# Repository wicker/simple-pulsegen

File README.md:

## Super Simple Function Generator

#### Waveform Generator IC

First off, I want to use a waveform generator IC. It seems like oscillators, audio waveform generators, and pulse generators are all limited kinds of waveform generator ICs. They all seem to cost less than the $10 chip I ended up with.

As far as full waveform generators go, the ICL8038 had an output frequency of up to 300kHz, and the derived MAX038 had an output frequency of up to 20MHz. Both chips are out of stock and no longer manufactured, so they're not an option for this project. 

I'm going to explore PLLs later on but for now I just want a chip that Just Works because the important thing is to generate my own signals. I could use the AD9833 or AD5930, both of which use direct digital synthesis (DDS) that converts a digital signal into an analog waveform.  

It's a tossup between AD9833 and AD5930. They both have 10 bit resolution and run on the same input range between 2.3V to 5.5V. 

AD9833 depends on 25MHz clock and is immediately available in quantity 1 for $9.27 at Digikey. 

AD5930 depends on a 50MHz clock and is not immediately available, and in any case it costs $13.40. And lo, another engineering decision decides itself. 

#### Using the AD9833 

It will produce sine, triangular, and square waves. No external components needed, except that it needs a microcontroller. The analog and digital grounds will need to be separated. It can create sine waves up to 12.5MHz. 

I don't understand how to build the chip itself, so I'm just going to put this on a breakout board and use it.

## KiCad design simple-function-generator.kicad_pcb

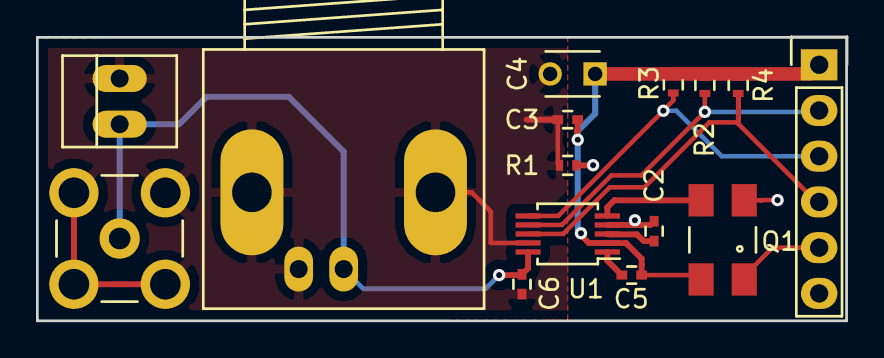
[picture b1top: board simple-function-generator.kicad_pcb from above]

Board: 2 copper layers, 45.0 x 15.7 mm, 15 parts (0 on the bottom side), 11 nets.

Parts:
C2, C3, C5, C6: 100nF; C_0402
C4: 10uF; C_Disc_D3_P2.5
P1: TO TEENSY 3.1+; Pin_Header_Straight_1x06
P2: SMA; SMB_Straight
P3: BNC; BNC_Socket_TYCO-AMP_LargePads
P4: TERMINAL; PINHEAD1-2
Q1: CB3-3C-25M0000; Crystal_SMD_0603_4Pads
R1: 0; R_0402
R2, R3, R4: DNP; R_0402
U1: AD9833; MSOP-10_3x3mm_Pitch0.5mm

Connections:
+5V: C3.1, C4.1, C5.1, P1.1, Q1.4, R2.1, R3.1, R4.1, U1.2
GNDA: C3.2, C4.2, C6.2, P2.2, P3.2, P4.2, R1.1, U1.9
GNDD: C2.2, P1.6, Q1.2, R1.2, U1.4
unnamed: C2.1, U1.3
unnamed: C5.2, U1.1
unnamed: C6.1, P2.1, P3.1, P4.1, U1.10
unnamed: P1.2, R2.2, U1.7
unnamed: P1.3, R3.2, U1.6
unnamed: P1.4, R4.2, U1.8
unnamed: P1.5, Q1.1
unnamed: Q1.3, U1.5

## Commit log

2016-04-15 Initial commit, just collecting everything in one place.

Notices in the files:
simple-function-generator.kicad_pcb:
Released under the CERN Open Hardware License v1.2
